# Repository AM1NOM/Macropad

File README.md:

# CONTROLA

Controla is a compact, tactile controller that brings your most-used shortcuts and actions within reach. It pairs responsive physical controls with a crisp OLED for clear status and feedback, so you always know what layer or mode you’re in. Perfect for switching tools, controlling media, or speeding up repetitive tasks, Controla fits neatly beside your keyboard and adapts to your workflow.

## Features
- RP2040-based Seeed XIAO module
- 0.91" SSD1306 I2C OLED display
- Rotary encoder with push
- 7x MX-style mechanical switches with per-key RGB (SK6812 MINI-E)
- Custom PCB and 3D printed case

## Screenshots

- **Schematic:**

- **PCB:**

- **CAD:**

## Bill of Materials (BOM)

| Ref | Qty | Part | Description |
|---|---:|---|---|
| U1 | 1 | Seeed XIAO RP2040 (SMD) | RP2040 MCU module, SMD mount |
| OLED1 | 1 | 0.91" OLED SSD1306 I2C | Pin order GND-VCC-SCL-SDA |
| ENC1 | 1 | EC11 Rotary Encoder w/ push | Volume / scroll encoder |
| KNOB1 | 1 | Encoder knob | Fits EC11 shaft |
| SW1-SW7 | 7 | MX-style mechanical switches | Keyboard switches |
| KEYCAPS | 7 | Blank DSA keycaps (white) | For MX switches |
| LED1-LED7 | 7 | SK6812 MINI-E RGB LEDs | Per-key RGB lighting |
| D1-D7 | 7 | 1N4148 diodes (TH) | Optional, for key matrix |
| PCB1 | 1 | Custom PCB | Macropad PCB |
| M3x16 | 4 | M3 x 16mm screws | Case mounting |
| HEATSET | 4 | M3 heatset inserts | For 3D printed case |
| CASE | 1 | 3D printed case | No acrylic |
| SOLDER_IRON | 1 | Soldering iron | Required for assembly |
| SOLDER | 1 | Solder wire 0.5mm | For TH + SMD |
| FLUX | 1 | Flux pen | Recommended for SMD |

For the complete, raw BOM file see [BOM.csv](BOM.csv).

## Assembly
1. Solder the Seeed XIAO to the PCB (SMD pad/module) or mount per module instructions.
2. Solder the OLED to the I2C pads (GND, VCC, SCL, SDA).
3. Place and solder mechanical switches and diodes (if used) in the key matrix.
4. Solder SK6812 LEDs and route their data line according to PCB silkscreen.
5. Mount the rotary encoder and knob; secure with nuts if required.
6. Install M3 heatset inserts in the 3D-printed case, secure PCB with M3x16 screws.

## Firmware
Firmware and microcontroller code are in `Firmware/main.py`.

## Other files
- PCB and schematic files: [PCB/hackpad.kicad_pcb](PCB/hackpad.kicad_pcb)
- PCB project files and library: `PCB/` folder
- 3D models for case: `CAD/` folder

## License
This project is open-source.

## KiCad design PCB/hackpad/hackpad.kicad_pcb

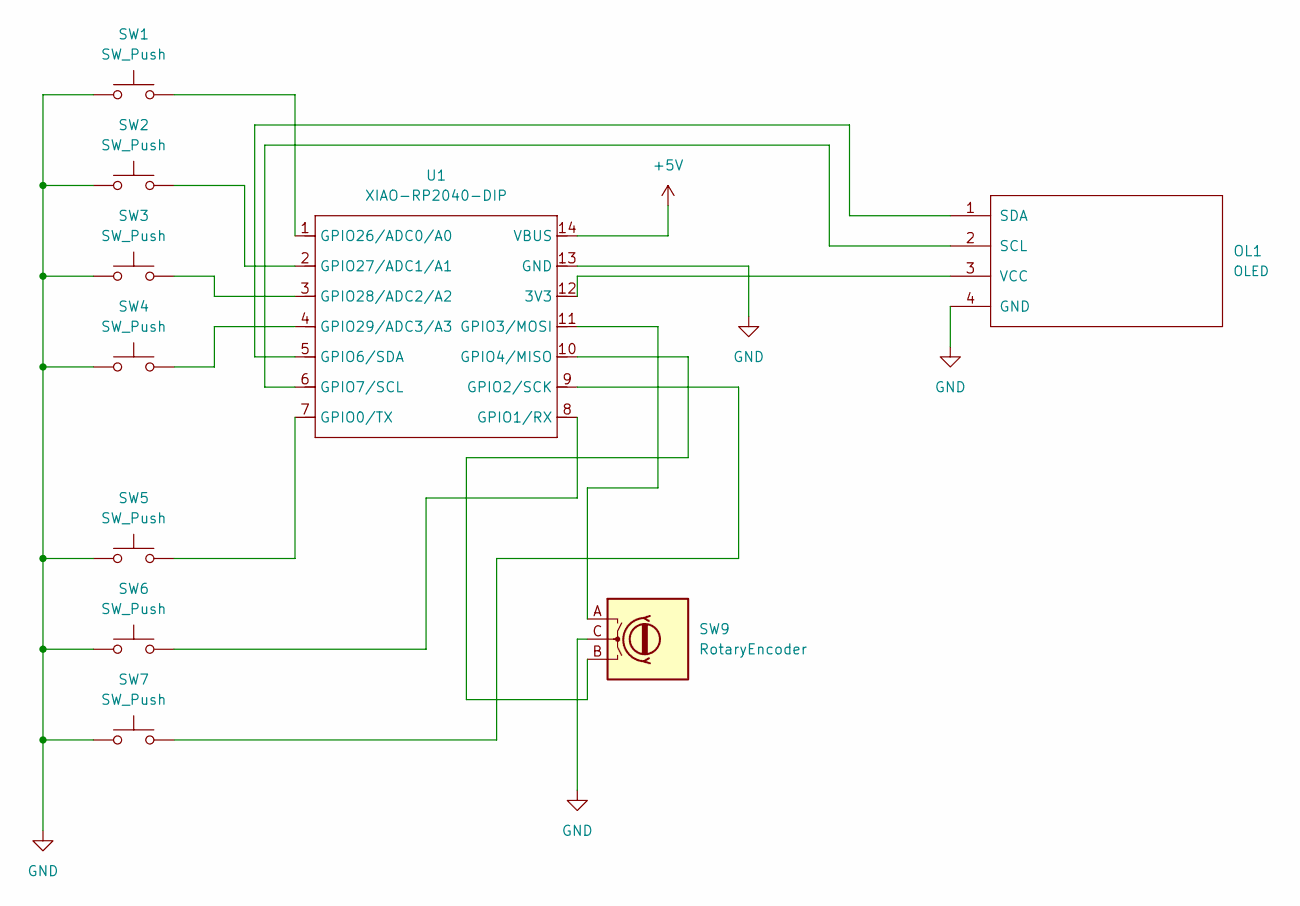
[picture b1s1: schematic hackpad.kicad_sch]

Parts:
OL1: OLED
SW1, SW2, SW3, SW4, SW5, SW6, SW7: SW_Push; SW_Cherry_MX_1.00u_PCB
SW9: RotaryEncoder; RotaryEncoder_Alps_EC11E_Vertical_H20mm
U1: XIAO-RP2040-DIP

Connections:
+5V: U1.14 (VBUS)
GND: OL1.4 (GND), SW1.1, SW2.1, SW3.1, SW4.1, SW5.1, SW6.1, SW7.1, SW9.C, U1.13 (GND)
unnamed: OL1.2 (SCL), U1.6 (GPIO7/SCL)
unnamed: OL1.1 (SDA), U1.5 (GPIO6/SDA)
unnamed: OL1.3 (VCC), U1.12 (3V3)
unnamed: SW5.2, U1.7 (GPIO0/TX)
unnamed: SW6.2, U1.8 (GPIO1/RX)
unnamed: SW7.2, U1.9 (GPIO2/SCK)
unnamed: SW9.A, U1.11 (GPIO3/MOSI)
unnamed: SW9.B, U1.10 (GPIO4/MISO)
unnamed: SW1.2, U1.1 (GPIO26/ADC0/A0)
unnamed: SW2.2, U1.2 (GPIO27/ADC1/A1)
unnamed: SW3.2, U1.3 (GPIO28/ADC2/A2)
unnamed: SW4.2, U1.4 (GPIO29/ADC3/A3)

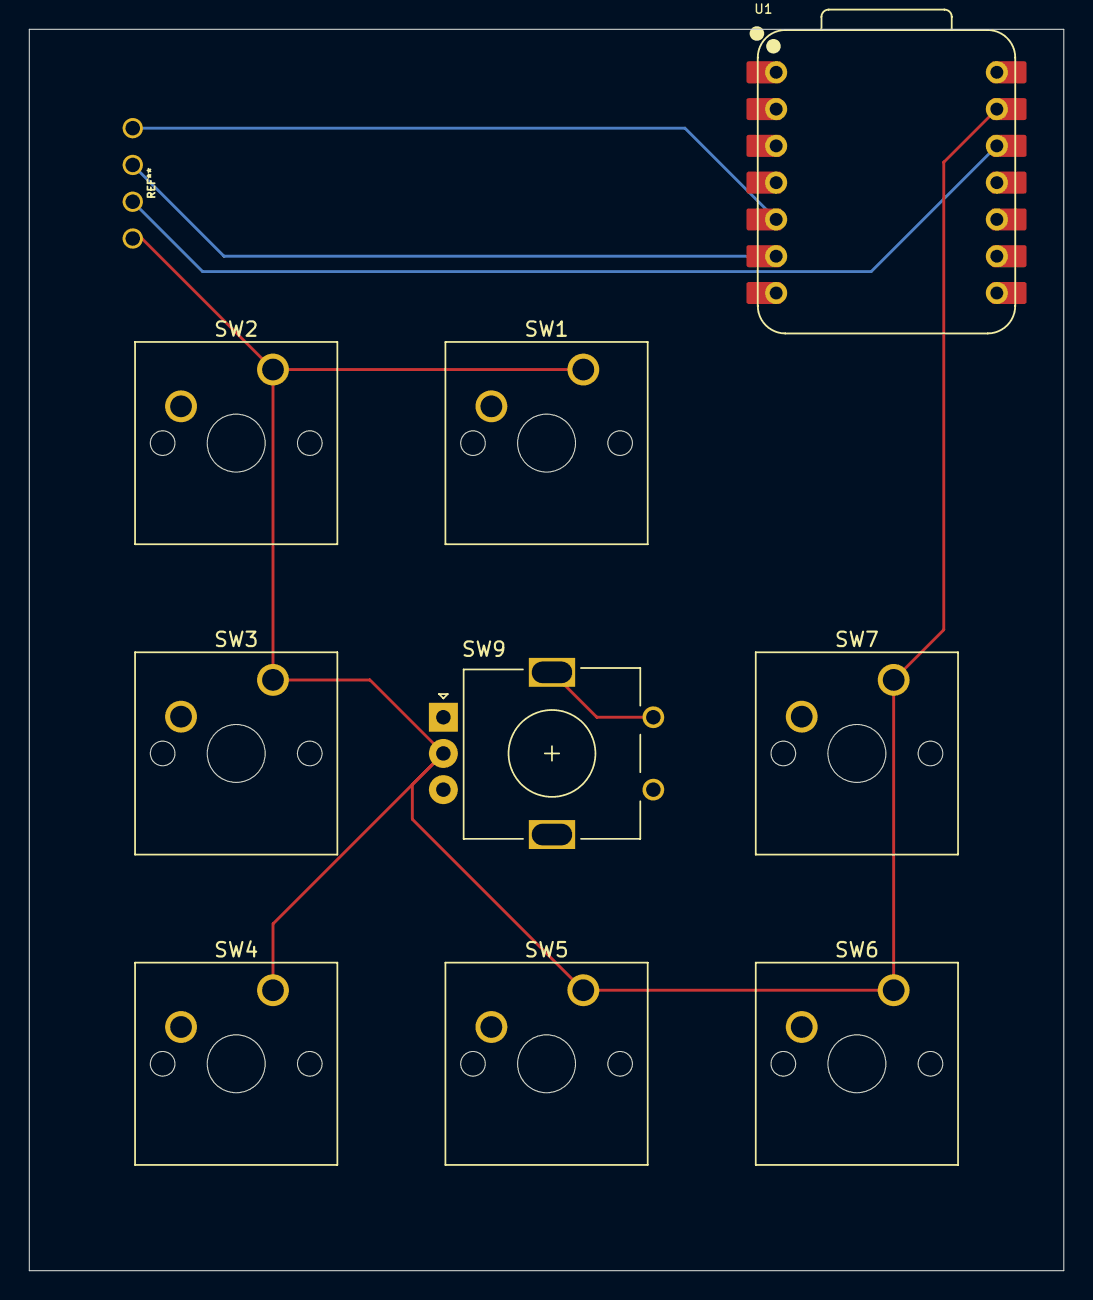
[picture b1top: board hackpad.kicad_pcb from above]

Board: 2 copper layers, 71.4 x 85.7 mm, 10 parts (0 on the bottom side), 13 nets.

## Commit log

2025-12-15 adding pcb files
2025-12-26 poof
2025-12-26 Add MIT License to the project
2025-12-26 new CAD files
2025-12-26 updated images in README
2025-12-26 updating README
